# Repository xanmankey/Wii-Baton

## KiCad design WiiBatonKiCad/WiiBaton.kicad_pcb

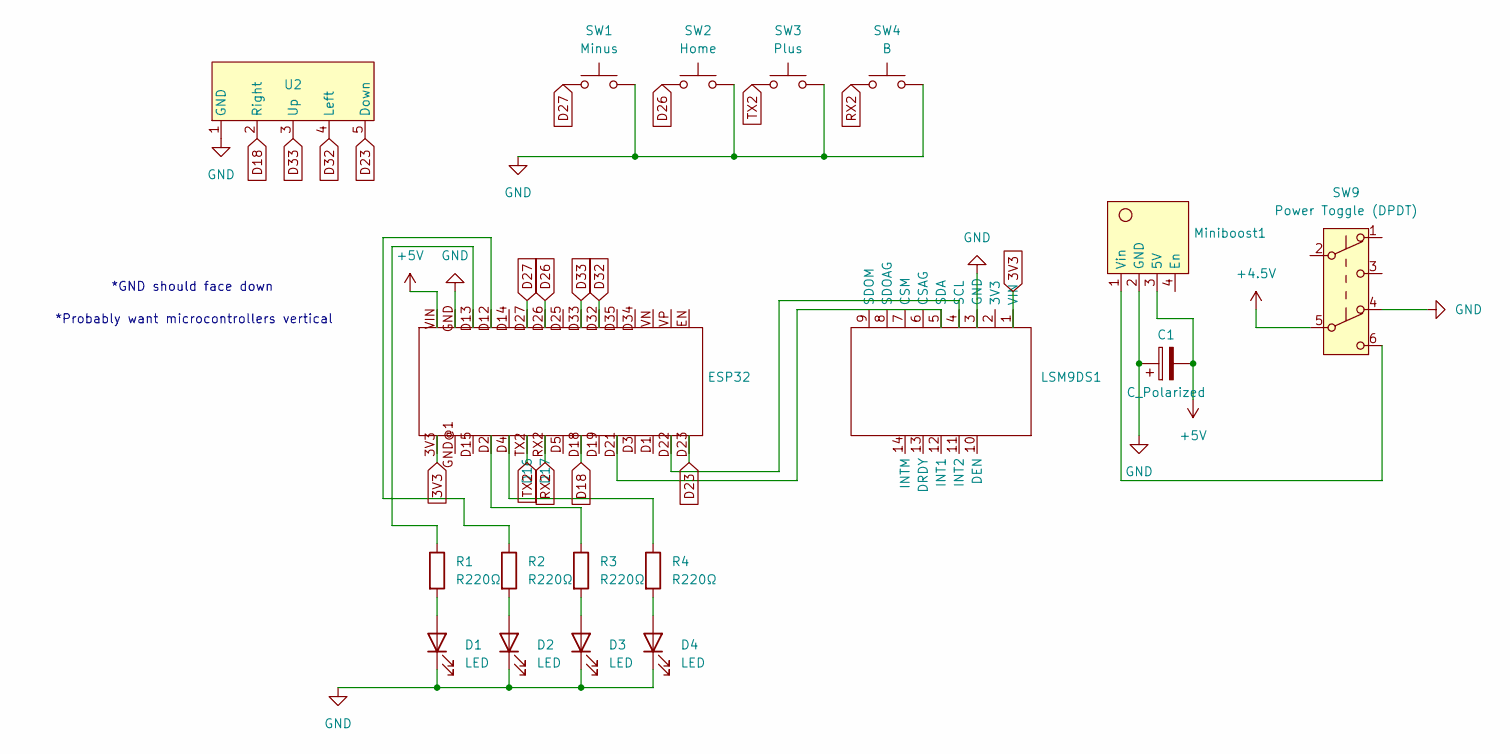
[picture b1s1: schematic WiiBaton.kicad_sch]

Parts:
C1: C_Polarized; C_Radial_D6.3mm_H5.0mm_P2.50mm
D1, D2, D3, D4: LED; LED_D3.0mm
ESP32: ESP32-DEVKITV1
LSM9DS1: LSM9DS1
Miniboost1: Miniboost
R1, R2, R3, R4: R220Ω; R_Axial_DIN0204_L3.6mm_D1.6mm_P2.54mm_Vertical
SW1: Minus; Membrane_Press_Button
SW2: Home; Membrane_Press_Button
SW3: Plus; Membrane_Press_Button
SW4: B; Membrane_Press_Button
SW9: Power Toggle (DPDT); 5.8mmDPDTSwitch
U2: Membrane_DPAD

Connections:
3V3: ESP32.3V3, LSM9DS1.1 (VIN)
+4.5V: SW9.5 (B)
+5V: C1.2, ESP32.VIN, Miniboost1.3 (5V)
D18: ESP32.D18, U2.2 (Right)
D23: ESP32.D23, U2.5 (Down)
D26: ESP32.D26, SW2.1
D27: ESP32.D27, SW1.1
D32: ESP32.D32, U2.4 (Left)
D33: ESP32.D33, U2.3 (Up)
GND: C1.1, D1.1 (K), D2.1 (K), D3.1 (K), D4.1 (K), ESP32.GND, LSM9DS1.3 (GND), Miniboost1.2 (GND), SW1.2, SW2.2, SW3.2, SW4.2, SW9.4 (A), U2.1 (GND)
unnamed: D1.2 (A), R1.2
unnamed: D2.2 (A), R2.2
unnamed: D3.2 (A), R3.2
unnamed: D4.2 (A), R4.2
unnamed: ESP32.D2, R3.1
unnamed: ESP32.D4, R4.1
unnamed: ESP32.D12, R2.1
unnamed: ESP32.D13, R1.1
unnamed: ESP32.D22, LSM9DS1.4 (SCL)
unnamed: ESP32.D21, LSM9DS1.5 (SDA)
unnamed: Miniboost1.1 (Vin), SW9.6 (C)
RX2: ESP32.RX2 (D17), SW4.1
TX2: ESP32.TX2 (D16), SW3.1

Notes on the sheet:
*Probably want microcontrollers vertical
*GND should face down

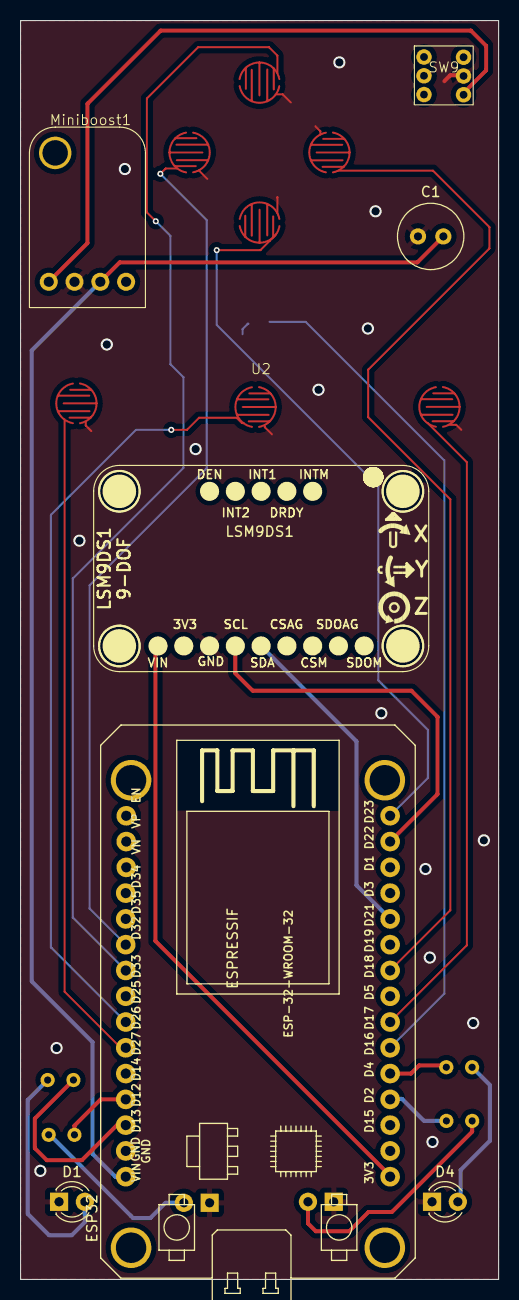
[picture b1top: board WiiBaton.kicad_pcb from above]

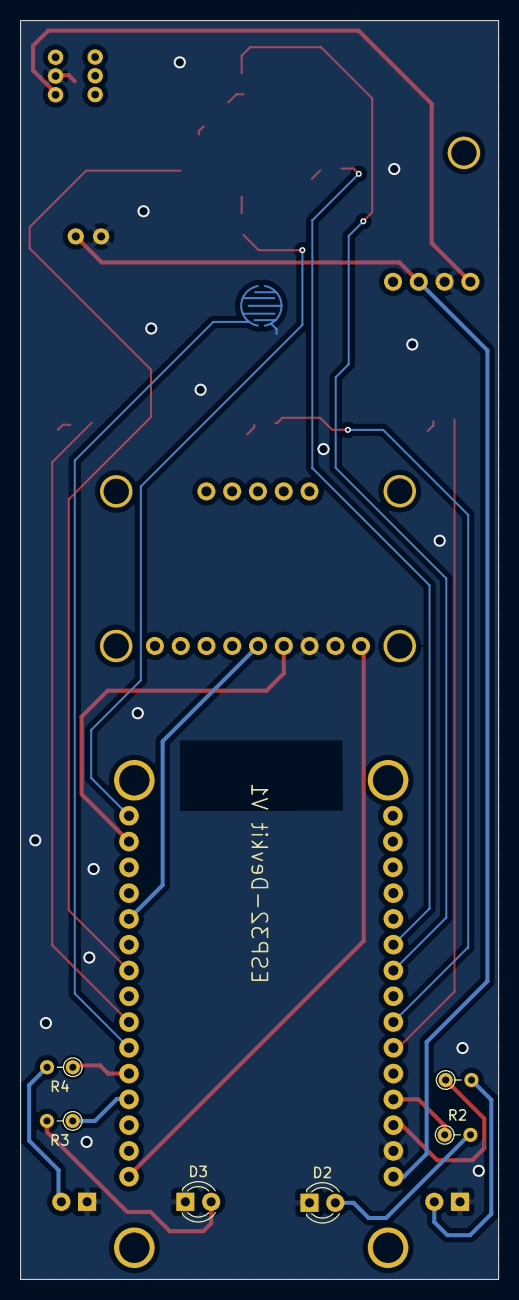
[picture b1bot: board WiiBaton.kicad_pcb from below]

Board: 2 copper layers, 47.1 x 124.0 mm, 18 parts (7 on the bottom side), 22 nets.

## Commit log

2026-02-19 removed venv
2026-02-19 added kicad files
2026-02-19 added profile pics and step files
